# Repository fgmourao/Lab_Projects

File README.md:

# NEURAL DYNAMICS DURING AUDITORY FEAR CONDITIONING

My main project carried out in the lab<br />
Postdoctoral researcher - PNPD/CAPES. Brazil

Flavio Mourao. Nucleo de Neurociencias - NNC<br />
email: mourao.fg@gmail.com<br />
Universidade Federal de Minas Gerais<br />
Brazil<br />
 
The relevance of sensory cues constantly changes in natural environments, and the adaptive behavior of animals depends on their ability to dynamically modulate the encoding of relevant stimuli. During auditory perception, the coordinated activity of the neuronal assemblies encoding acoustic stimuli results in oscillatory patterns of local field potential (LFP). Over the last several years, it has been reported that auditory learning modifies the encoding of behaviorally relevant sounds and influences LFP oscillations in different auditory brain areas. In auditory fear conditioning (AFC), pairing an auditory conditioned stimulus (CS) with a foot shock modifies the neural oscillations in the brain areas involved in CS processing.

Much of the recent effort to understand the underpinnings of this constructive nature of perception has been put into the modulation exerted by the cortex into the thalamus and/or limbic areas. However, some features of the incoming stimuli are processed in the very first stages of the sensory pathway, some of them being the target of robust efferent projections from higher-level processing areas and being subjected to task-related plastic changes. 

In this sense, we propose to analyze the relationships between multiple brain substrates along the acoustic pathway involved in different stages of auditory perception.

Previous papers : <br />
Lockmann & Mourao, 2017         ->  https://doi.org/10.1152/jn.00293.2017<br />
Amaral-Junior & Mourao, 2019    ->  https://doi.org/10.3389/fnins.2019.01193<br />
Simoes & Mourao, 2020.          ->  https://doi.org/10.1016/j.neulet.2020.135311

Midbrain local field potential oscillations follow the amplitude envelope of an amplitude-modulated tone, originating a neural response called the steady-state evoked potential.

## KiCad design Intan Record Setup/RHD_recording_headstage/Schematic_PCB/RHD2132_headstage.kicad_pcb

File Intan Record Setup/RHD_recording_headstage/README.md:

# Headstage adapted from the Intan RHD headstage system<br />

<br />

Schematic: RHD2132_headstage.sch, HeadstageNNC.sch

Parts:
C1, C3: 100n; R_0603
C2: 10n; R_0603
J1, J2: FFCfemale20
J3: AuxInputs; Pin_Header_Straight_1x03_Pitch2.00mm
J4: SPI; JumperSPI2
J5: POWER; Pin_Header_Straight_1x02_Pitch2.00mm
J6, J7: Conn_01x01; Pin_Header_Straight_1x01_Pitch2.00mm
R1, R2, R3: 0; R_0603
U1: RHD2132_QFN; RHD2000-QFN56_8_X_8_LARGE

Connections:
/N$42: C2.1, U1.28 (ADC_REF)
/N$43: U1.27 (AUXOUT)
AUXIN1: J3.1, U1.14 (AUXIN1)
AUXIN2: J3.2, U1.15 (AUXIN2)
AUXIN3: J3.3, U1.16 (AUXIN3)
CH0: J1.3, U1.9 (IN0)
CH1: J1.4, U1.8 (IN1)
CH2: J1.5, U1.7 (IN2)
CH3: J1.6, U1.6 (IN3)
CH4: J1.7, U1.5 (IN4)
CH5: J1.8, U1.4 (IN5)
CH6: J1.9, U1.3 (IN6)
CH7: J1.10, U1.2 (IN7)
CH8: J1.11, U1.1 (IN8)
CH9: J1.13, U1.56 (IN9)
CH10: J1.15, U1.55 (IN10)
CH11: J1.17, U1.54 (IN11)
CH12: J1.16, U1.53 (IN12)
CH13: J1.18, U1.52 (IN13)
CH14: J1.14, U1.51 (IN14)
CH15: J1.12, U1.50 (IN15)
CH16: J2.13, U1.49 (IN16)
CH17: J2.17, U1.48 (IN17)
CH18: J2.15, U1.47 (IN18)
CH19: J2.18, U1.46 (IN19)
CH20: J2.16, U1.45 (IN20)
CH21: J2.14, U1.44 (IN21)
CH22: J2.12, U1.43 (IN22)
CH23: J2.11, U1.42 (IN23)
CH24: J2.10, U1.41 (IN24)
CH25: J2.9, U1.40 (IN25)
CH26: J2.8, U1.39 (IN26)
CH27: J2.7, U1.38 (IN27)
CH28: J2.6, U1.37 (IN28)
CH29: J2.5, U1.36 (IN29)
CH30: J2.4, U1.35 (IN30)
CH31: J2.3, U1.34 (IN31)
GND: C1.2, C2.2, C3.2, J1.1, J1.20, J2.1, J2.20, J5.1, R1.1, R3.1, U1.11 (GND1), U1.12 (GND2), U1.17 (GND3), U1.29 (GND4), U1.32 (VESD), U1.CENT (CTR)
MISO+: J4.8, U1.25 (MISO+)
MISO-: J4.7, U1.24 (MISO-)
MOSI+: J4.6, U1.23 (MOSI+)
MOSI-: J4.5, U1.22 (MOSI-)
unnamed: R1.2, R2.2, U1.30 (LVDS_EN)
REF_ELECTRODE: J1.2, J1.19, J2.2, J2.19, R3.2, U1.10 (REF_ELEC)
SCLK+: J4.4, U1.21 (SCLK+)
SCLK-: J4.3, U1.20 (SCLK-)
VCC: C1.1, C3.1, J5.2, R2.1, U1.13 (VDD1), U1.26 (VDD2), U1.31 (VDD3)
~CS~+: J4.2, U1.19 (~CS~+)
~CS~-: J4.1, U1.18 (~CS~-)

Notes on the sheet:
RHD2132 Intan Chip
FFC Connectors
Select between LVDS and CMOS
Jumpers
Mechanical support
LVDS
CMOS
Select between RHD2216 and RHD2132
This resistor must be soldered when using RHD2216.
Unconnected

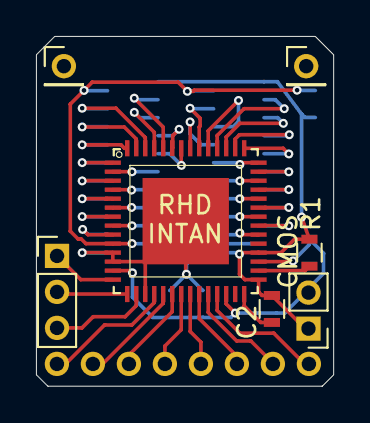
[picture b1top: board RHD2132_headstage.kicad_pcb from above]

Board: 4 copper layers, 16.5 x 19.4 mm, 14 parts (0 on the bottom side), 48 nets.

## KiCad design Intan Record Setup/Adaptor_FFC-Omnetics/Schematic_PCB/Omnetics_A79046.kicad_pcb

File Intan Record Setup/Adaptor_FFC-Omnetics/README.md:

# Adapters

RHD 16-Channel Recording Headstages<br />

<br />

RHD 32-Channel Recording Headstages<br />

<br />

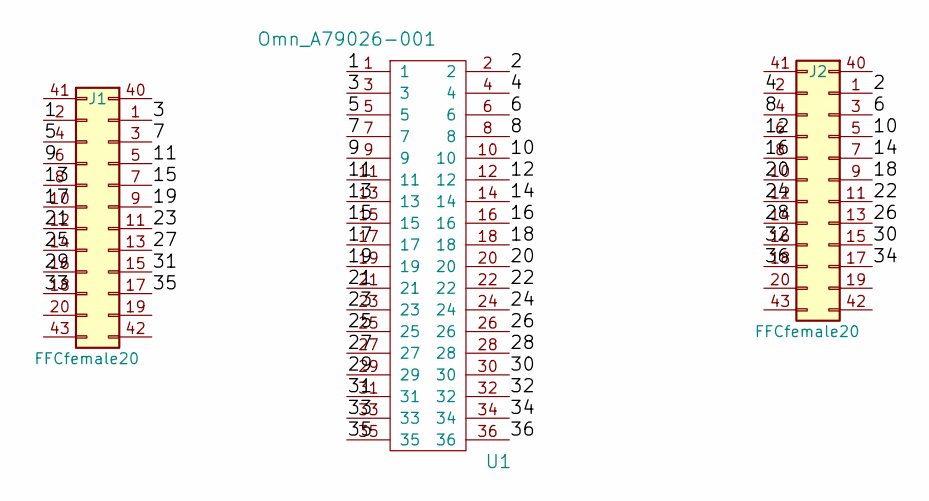
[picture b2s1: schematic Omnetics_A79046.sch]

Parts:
J1, J2: FFCfemale20
U1: Omn_A79026-001; Omn_A79026_pin

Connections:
/1: J1.2, U1.1
/2: J2.1, U1.2
/3: J1.1, U1.3
/4: J2.2, U1.4
/5: J1.4, U1.5
/6: J2.3, U1.6
/7: J1.3, U1.7
/8: J2.4, U1.8
/9: J1.6, U1.9
/10: J2.5, U1.10
/11: J1.5, U1.11
/12: J2.6, U1.12
/13: J1.8, U1.13
/14: J2.7, U1.14
/15: J1.7, U1.15
/16: J2.8, U1.16
/17: J1.10, U1.17
/18: J2.9, U1.18
/19: J1.9, U1.19
/20: J2.10, U1.20
/21: J1.12, U1.21
/22: J2.11, U1.22
/23: J1.11, U1.23
/24: J2.12, U1.24
/25: J1.14, U1.25
/26: J2.13, U1.26
/27: J1.13, U1.27
/28: J2.14, U1.28
/29: J1.16, U1.29
/30: J2.15, U1.30
/31: J1.15, U1.31
/32: J2.16, U1.32
/33: J1.18, U1.33
/34: J2.17, U1.34
/35: J1.17, U1.35
/36: J2.18, U1.36

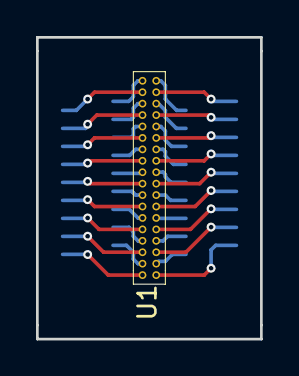
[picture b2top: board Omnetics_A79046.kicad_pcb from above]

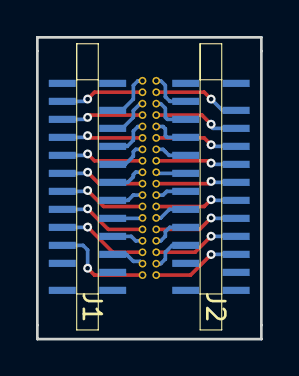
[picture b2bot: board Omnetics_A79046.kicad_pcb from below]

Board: 2 copper layers, 12.4 x 16.8 mm, 3 parts (2 on the bottom side), 36 nets.

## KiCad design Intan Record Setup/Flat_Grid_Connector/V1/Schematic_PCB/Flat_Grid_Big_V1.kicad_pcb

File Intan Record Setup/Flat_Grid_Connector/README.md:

# Flat-Grid Connector <br />

V2 - Current Version<br />

<br />

V1 - Old Version<br />

<br />

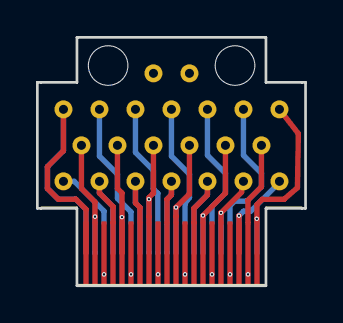
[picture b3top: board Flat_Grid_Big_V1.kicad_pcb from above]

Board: 2 copper layers, 14.9 x 13.8 mm, 3 parts (1 on the bottom side), 20 nets.

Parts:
Edge1, Edge2: Conn_01x20; FFCmale20_semvias
Holes1: Conn_01x20; FFCmalePINarray

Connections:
unnamed: Edge1.1, Edge2.20, Holes1.1
unnamed: Edge1.2, Edge2.19, Holes1.2
unnamed: Edge1.3, Edge2.18, Holes1.3
unnamed: Edge1.4, Edge2.17, Holes1.4
unnamed: Edge1.5, Edge2.16, Holes1.5
unnamed: Edge1.6, Edge2.15, Holes1.6
unnamed: Edge1.7, Edge2.14, Holes1.7
unnamed: Edge1.8, Edge2.13, Holes1.8
unnamed: Edge1.9, Edge2.12, Holes1.9
unnamed: Edge1.10, Edge2.11, Holes1.10
unnamed: Edge1.11, Edge2.10, Holes1.11
unnamed: Edge1.12, Edge2.9, Holes1.12
unnamed: Edge1.13, Edge2.8, Holes1.13
unnamed: Edge1.14, Edge2.7, Holes1.14
unnamed: Edge1.15, Edge2.6, Holes1.15
unnamed: Edge1.16, Edge2.5, Holes1.16
unnamed: Edge1.17, Edge2.4, Holes1.17
unnamed: Edge1.18, Edge2.3, Holes1.18
unnamed: Edge1.19, Edge2.2, Holes1.19
unnamed: Edge1.20, Edge2.1, Holes1.20

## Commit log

2020-04-10 updated GUI_vid
    code tidying up and translations
2020-04-12 update 11-04-20
2020-04-13 update 13-04-20
2020-04-14 update - 13/04/20
2020-04-16 update 16-04-20
2020-04-20 update 20-04-20
2020-04-26 update 26-04-20
2020-05-10 update 10-05-20
2020-05-14 update14-05-20
2020-05-27 update 27-05-20
2020-06-02 update 01-06-20
2020-09-12 update_12-09-2020
    create animation from modulation index values
2020-09-14 update 14-09-2020
2020-09-21 update 20-09-20
    improve functions
2021-03-31 Update 31-03-21
2021-03-31 Update 31-03-2021
2021-04-03 Update 04-2021
2021-04-20 update 20-04-21
